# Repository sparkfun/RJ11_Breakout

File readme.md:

RJ11 Breakout
=======

A simple breakout board for the common 6-pin RJ11 connector. Works with common 4-wire telephone cable. Board has standard Black/Red/Yellow/Green labels on the top of the board to match the telephone cable widely used. Board has pin numbers on the back side of the board that match with the pins on the connector.

This is designed to be a panel of two with snappable mounting holes.

License Information
-------------------

The hardware is released under [Creative Commons Share-alike 4.0](http://creativecommons.org/licenses/by-sa/4.0/).  
The firmware is released under the [Beerware license](http://en.wikipedia.org/wiki/Beerware).

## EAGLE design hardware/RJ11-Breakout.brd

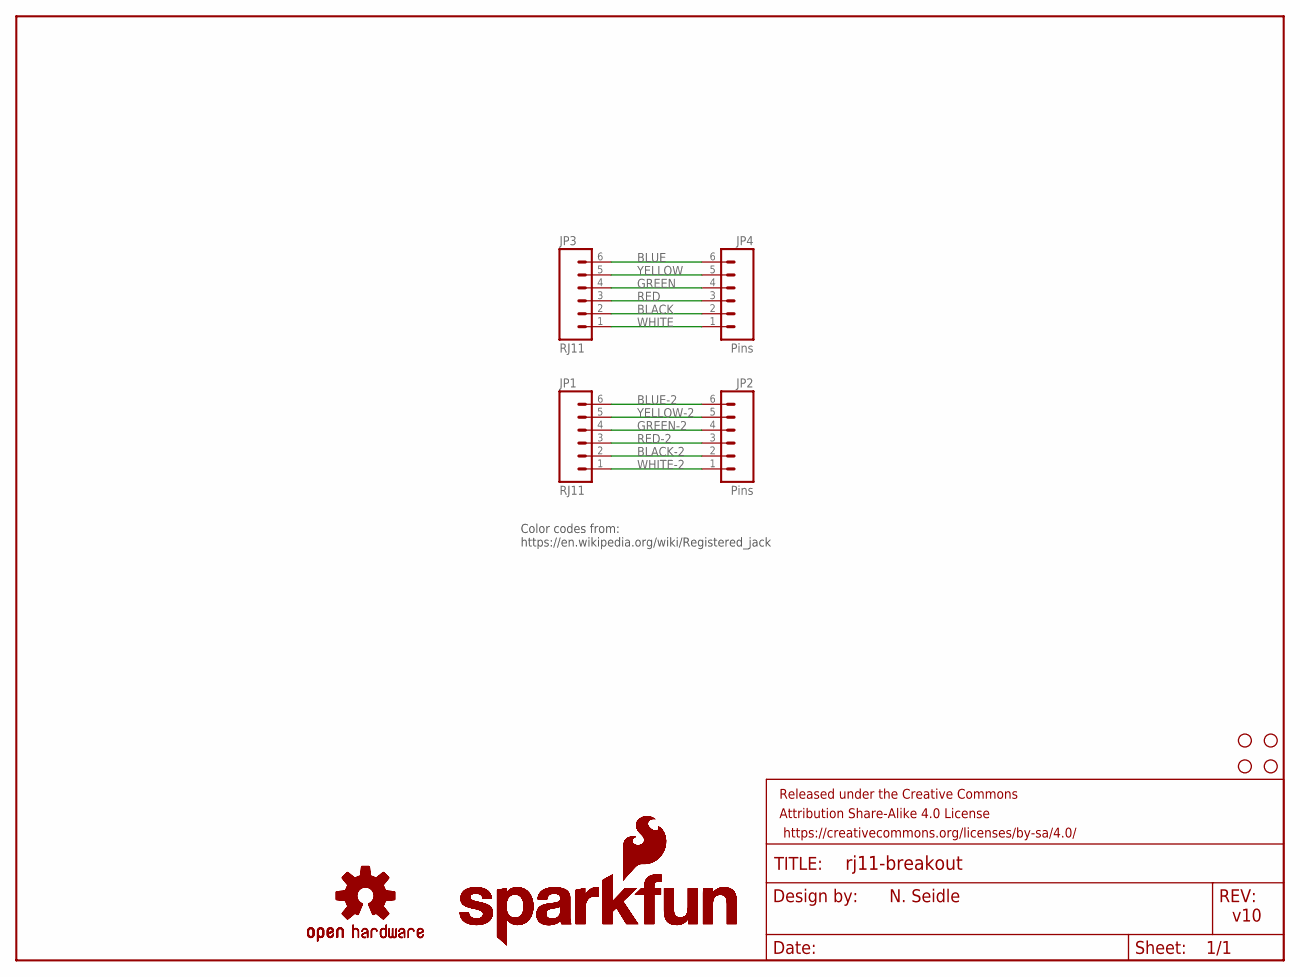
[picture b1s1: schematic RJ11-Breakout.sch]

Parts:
FRAME2: FRAME-LETTER; CREATIVE_COMMONS
H1, H2, H3, H4: STAND-OFF
JP1, JP3: RJ11; RJ11-6
JP2, JP4: Pins; 1X06
LOGO1, LOGO2, LOGO4, LOGO5: SFE_LOGO_NAME_FLAME.1_INCH; SFE_LOGO_NAME_FLAME_.1
LOGO3, LOGO6: OSHW-LOGOMINI; OSHW-LOGO-MINI

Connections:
BLACK: JP3.2, JP4.2
BLACK-2: JP1.2, JP2.2
BLUE: JP3.6, JP4.6
BLUE-2: JP1.6, JP2.6
GREEN: JP3.4, JP4.4
GREEN-2: JP1.4, JP2.4
RED: JP3.3, JP4.3
RED-2: JP1.3, JP2.3
WHITE: JP3.1, JP4.1
WHITE-2: JP1.1, JP2.1
YELLOW: JP3.5, JP4.5
YELLOW-2: JP1.5, JP2.5

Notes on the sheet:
N. Seidle
v10
Color codes from: https://en.wikipedia.org/wiki/Registered_jack

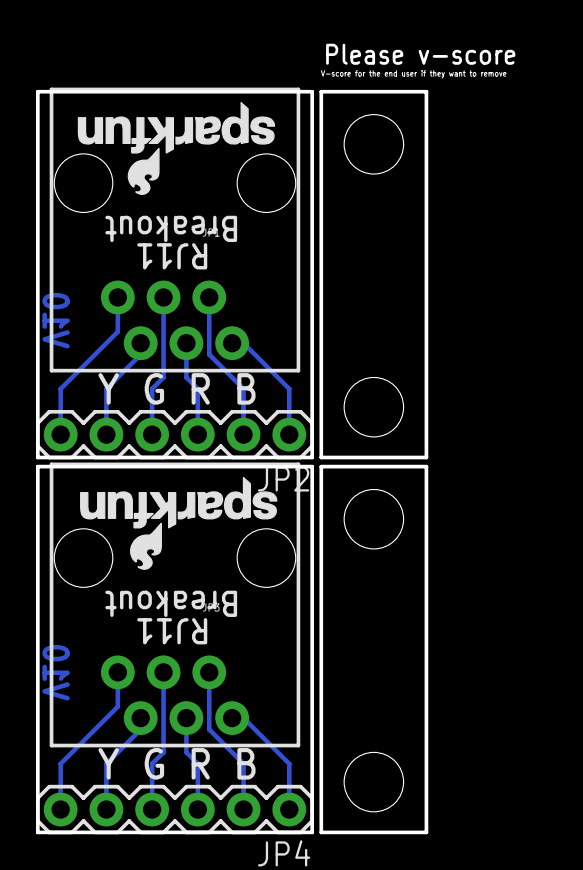
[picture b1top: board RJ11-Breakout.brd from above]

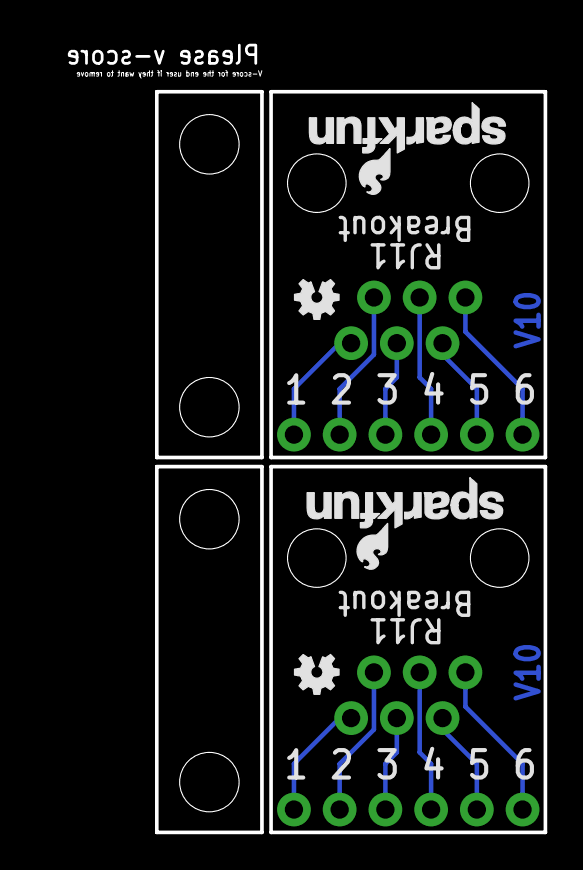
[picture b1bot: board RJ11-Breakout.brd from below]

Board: 2 copper layers, 21.6 x 41.1 mm, 15 parts (4 on the bottom side), 12 nets.

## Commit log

2016-08-18 :space_invader: Added .gitattributes & .gitignore files
2016-08-18 Readme update
2016-08-23 Added gear, version, dimensions, mounting holes with v-score.
2016-08-23 Fixes to address issue 1
2016-08-24 Creating panel of two
2016-10-04 Updating readme to include images

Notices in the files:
parts and their libraries:
SparkFun-Aesthetics: Licensing: CC v3.0 Share-Alike You are welcome to use this library for commercial purposes.
SparkFun-Aesthetics: Released under the Creative Commons Attribution Share-Alike 4.0 License
SparkFun-Aesthetics: https://creativecommons.org/licenses/by-sa/4.0
